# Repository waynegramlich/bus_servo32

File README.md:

# bus_servo32

This is really a template for `bus_servoN` modules, where
N is a multiple of 4.

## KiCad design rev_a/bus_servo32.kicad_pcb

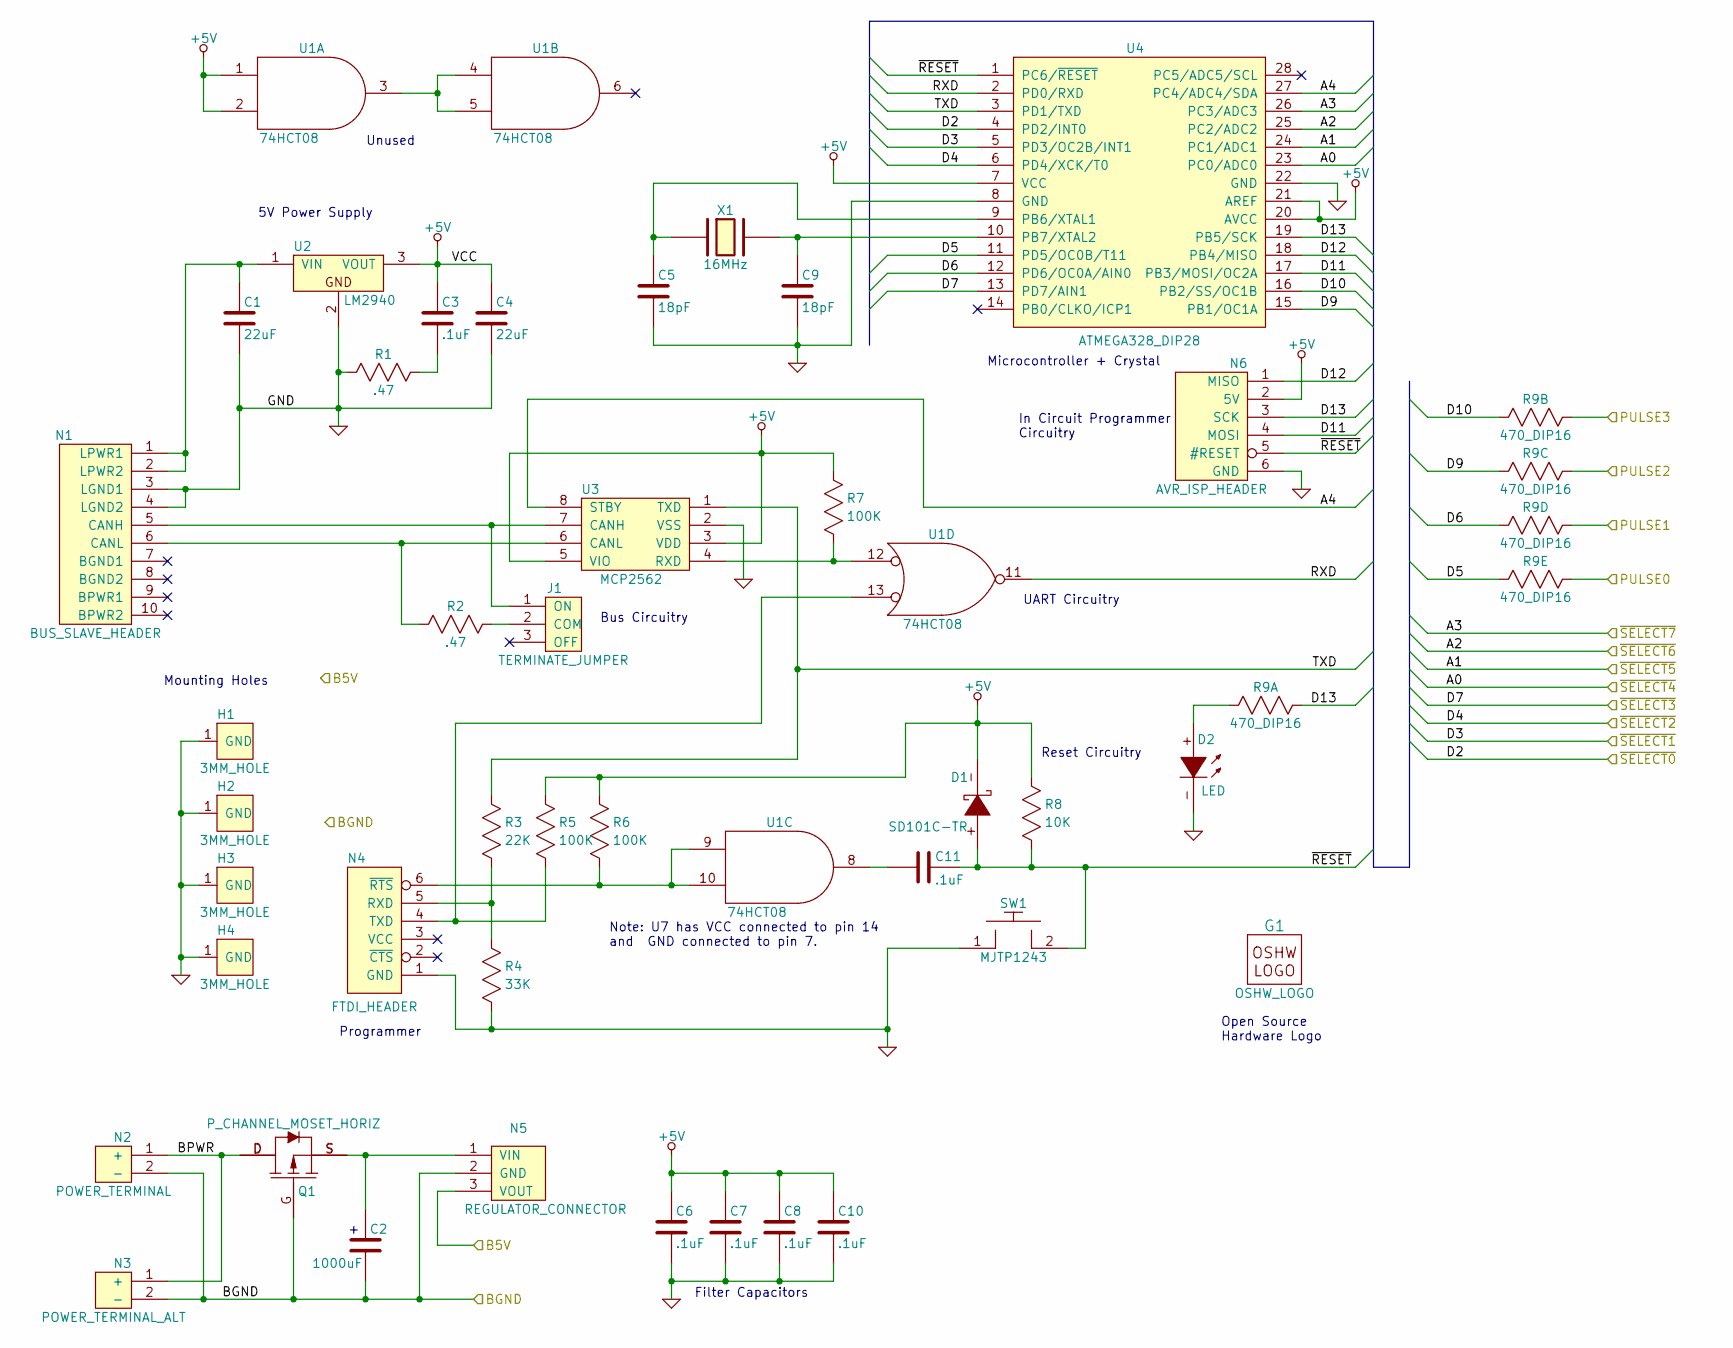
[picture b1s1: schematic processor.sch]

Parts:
C1, C4: 22uF; Capacitor3MMDiscRM2.5
C2: 1000uF; Capacitor4x3RM2-5_RevB
C3, C6, C7, C8, C10, C11: .1uF; Capacitor4x3RM2-5_RevB
C5, C9: 18pF; Capacitor4x3RM2-5_RevB
D1: SD101C-TR; Diode_DO-41_SOD81_Horizontal_RM10
D2: LED; T1_LED
G1: OSHW_LOGO; OSHW_LOGO_300mil
H1, H2, H3, H4: 3MM_HOLE; MountingHole_3mm
J1: TERMINATE_JUMPER; Pin_Header_Straight_1x03
N1: BUS_SLAVE_HEADER; Pin_Header_Straight_2x05_Shrouded
N2: POWER_TERMINAL; 5MM_TERMINAL_BLOCK_2_POS
N3: POWER_TERMINAL_ALT; 5MM_TERMINAL_BLOCK_2_POS
N4: FTDI_HEADER; Pin_Header_Straight_1x06
N5: REGULATOR_CONNECTOR; Pin_Header_Straight_1x03
N6: AVR_ISP_HEADER; Pin_Header_Straight_2x03
Q1: P_CHANNEL_MOSET_HORIZ; TO-220_Neutral123_Horizontal_LargePads
R1, R2: .47; Resistor_Horizontal_400
R3: 22K; Resistor_Horizontal_400
R4: 33K; Resistor_Horizontal_400
R5, R6, R7: 100K; Resistor_Horizontal_400
R8: 10K; Resistor_Horizontal_400
R9: 470_DIP16; DIP-16__300
SW1: MJTP1243; Button_6.5MM
U1: 74HCT08; DIP-14__300
U2: LM2940; TO-220_Neutral123_Horizontal_LargePads
U3: MCP2562; DIP-8__300
U4: ATMEGA328_DIP28; DIP-28__300
X1: 16MHz; Crystal_HC49-U_Vertical

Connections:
+5V: C3.1, C4.1, C6.1, C7.1, C8.1, C10.1, D1.-, N6.2 (5V), R5.2, R6.2, R7.2, R8.2, U1.1, U1.2, U1.14 (VCC), U2.3 (VOUT), U3.3 (VDD), U3.5 (VIO), U4.7 (VCC), U4.20 (AVCC), U4.21 (AREF)
/Processor/A4: U3.8 (STBY), U4.27 (PC4/ADC4/SDA)
/Processor/B5V: N5.3 (VOUT); also elsewhere on the board
/Processor/BGND: C2.2, N2.2 (-), N3.2 (-), N5.2 (GND), Q1.G; also elsewhere on the board
/Processor/BPWR: N2.1 (+), N3.1 (+), Q1.D
/Processor/D5: R9.5 (A), U4.11 (PD5/OC0B/T11)
/Processor/D6: R9.4 (A), U4.12 (PD6/OC0A/AIN0)
/Processor/D9: R9.3 (A), U4.15 (PB1/OC1A)
/Processor/D10: R9.2 (A), U4.16 (PB2/SS/OC1B)
/Processor/D11: N6.4 (MOSI), U4.17 (PB3/MOSI/OC2A)
/Processor/D12: N6.1 (MISO), U4.18 (PB4/MISO)
/Processor/D13: N6.3 (SCK), R9.16 (B), U4.19 (PB5/SCK)
/Processor/PULSE0: R9.12 (B); also elsewhere on the board
/Processor/PULSE1: R9.13 (B); also elsewhere on the board
/Processor/PULSE2: R9.14 (B); also elsewhere on the board
/Processor/PULSE3: R9.15 (B); also elsewhere on the board
/Processor/RXD: U1.11, U4.2 (PD0/RXD)
/Processor/TXD: R3.2, U3.1 (TXD), U4.3 (PD1/TXD)
/Processor/~RESET: C11.2, D1.+, N6.5 (#RESET), R8.1, SW1.2, U4.1 (PC6/~RESET)
/Processor/~SELECT0: U4.4 (PD2/INT0); also elsewhere on the board
/Processor/~SELECT1: U4.5 (PD3/OC2B/INT1); also elsewhere on the board
/Processor/~SELECT2: U4.6 (PD4/XCK/T0); also elsewhere on the board
/Processor/~SELECT3: U4.13 (PD7/AIN1); also elsewhere on the board
/Processor/~SELECT4: U4.23 (PC0/ADC0); also elsewhere on the board
/Processor/~SELECT5: U4.24 (PC1/ADC1); also elsewhere on the board
/Processor/~SELECT6: U4.25 (PC2/ADC2); also elsewhere on the board
/Processor/~SELECT7: U4.26 (PC3/ADC3); also elsewhere on the board
GND: C1.2, C4.2, C5.2, C6.2, C7.2, C8.2, C9.2, C10.2, D2.-, H1.1, H2.1, H3.1, H4.1, N1.3 (LGND1), N1.4 (LGND2), N4.1 (GND), N6.6 (GND), R1.1, R4.1, SW1.1, U1.7 (GND), U2.2, U3.2 (VSS), U4.8 (GND), U4.22 (GND)
unnamed: C1.1, N1.1 (LPWR1), N1.2 (LPWR2), U2.1 (VIN)
unnamed: C2.1, N5.1 (VIN), Q1.S
unnamed: C3.2, R1.2
unnamed: C5.1, U4.9 (PB6/XTAL1), X1.1
unnamed: C9.1, U4.10 (PB7/XTAL2), X1.2
unnamed: C11.1, U1.8
unnamed: D2.+, R9.1 (A)
unnamed: J1.1 (ON), N1.5 (CANH), U3.7 (CANH)
unnamed: J1.2 (COM), R2.2
unnamed: N1.6 (CANL), R2.1, U3.6 (CANL)
unnamed: N4.4 (TXD), R5.1, U1.13
unnamed: N4.5 (RXD), R3.1, R4.2
unnamed: N4.6 (~RTS), R6.1, U1.9, U1.10
unnamed: R7.1, U1.12, U3.4 (RXD)
unnamed: U1.3, U1.4, U1.5

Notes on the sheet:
Filter Capacitors
Reset Circuitry
Programmer
UART Circuitry
5V Power Supply
Unused
Note: U7 has VCC connected to pin 14 and GND connected to pin 7.
In Circuit Programmer Circuitry
Bus Circuitry
Mounting Holes
Open Source Hardware Logo
Microcontroller + Crystal

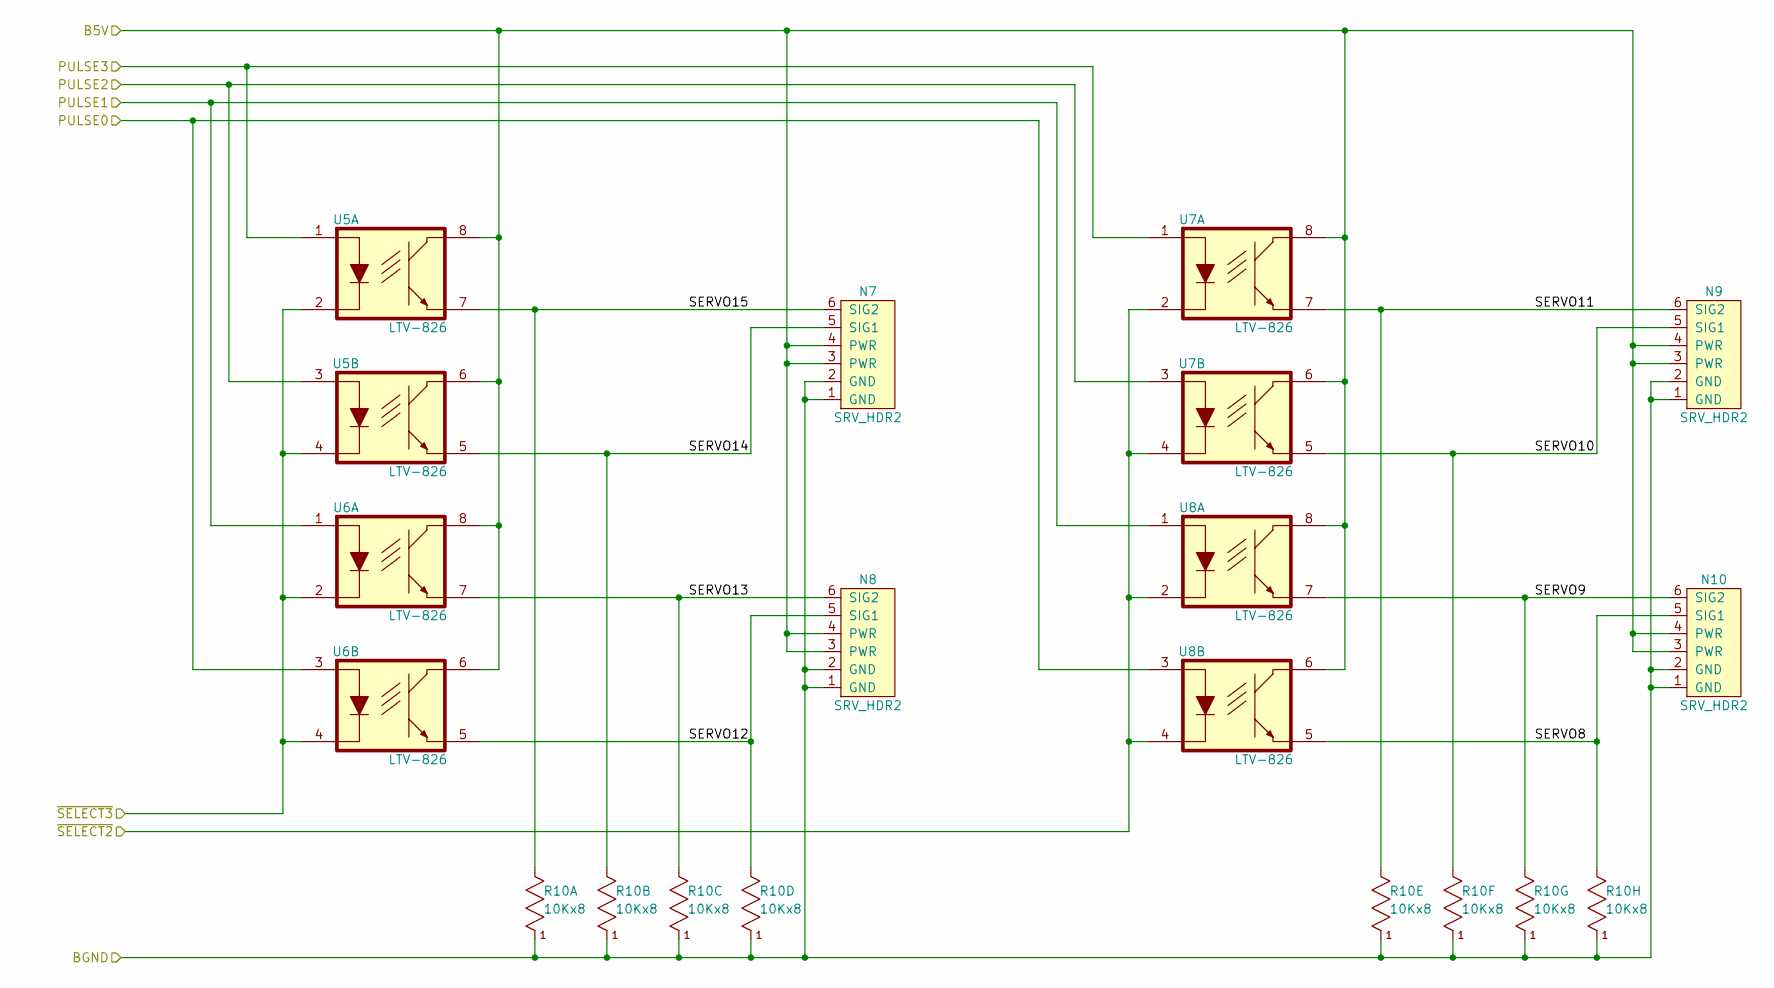
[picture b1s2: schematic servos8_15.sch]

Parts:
N7, N8, N9, N10: SRV_HDR2; Pin_Header_Straight_2x03
R10: 10Kx8; Pin_Header_Straight_1x09
U5, U6, U7, U8: LTV-826; DIP-8__300

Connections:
/Processor/B5V: N7.3 (PWR), N7.4 (PWR), N8.3 (PWR), N8.4 (PWR), N9.3 (PWR), N9.4 (PWR), N10.3 (PWR), N10.4 (PWR), U5.6, U5.8, U6.6, U6.8, U7.6, U7.8, U8.6, U8.8; also elsewhere on the board
/Processor/BGND: N7.1 (GND), N7.2 (GND), N8.1 (GND), N8.2 (GND), N9.1 (GND), N9.2 (GND), N10.1 (GND), N10.2 (GND), R10.1; also elsewhere on the board
/Processor/PULSE0: U6.3, U8.3; also elsewhere on the board
/Processor/PULSE1: U6.1, U8.1; also elsewhere on the board
/Processor/PULSE2: U5.3, U7.3; also elsewhere on the board
/Processor/PULSE3: U5.1, U7.1; also elsewhere on the board
/Processor/~SELECT2: U7.2, U7.4, U8.2, U8.4; also elsewhere on the board
/Processor/~SELECT3: U5.2, U5.4, U6.2, U6.4; also elsewhere on the board
/Servos_8:15/SERVO8: N10.5 (SIG1), R10.9, U8.5
/Servos_8:15/SERVO9: N10.6 (SIG2), R10.8, U8.7
/Servos_8:15/SERVO10: N9.5 (SIG1), R10.7, U7.5
/Servos_8:15/SERVO11: N9.6 (SIG2), R10.6, U7.7
/Servos_8:15/SERVO12: N8.5 (SIG1), R10.5, U6.5
/Servos_8:15/SERVO13: N8.6 (SIG2), R10.4, U6.7
/Servos_8:15/SERVO14: N7.5 (SIG1), R10.3, U5.5
/Servos_8:15/SERVO15: N7.6 (SIG2), R10.2, U5.7

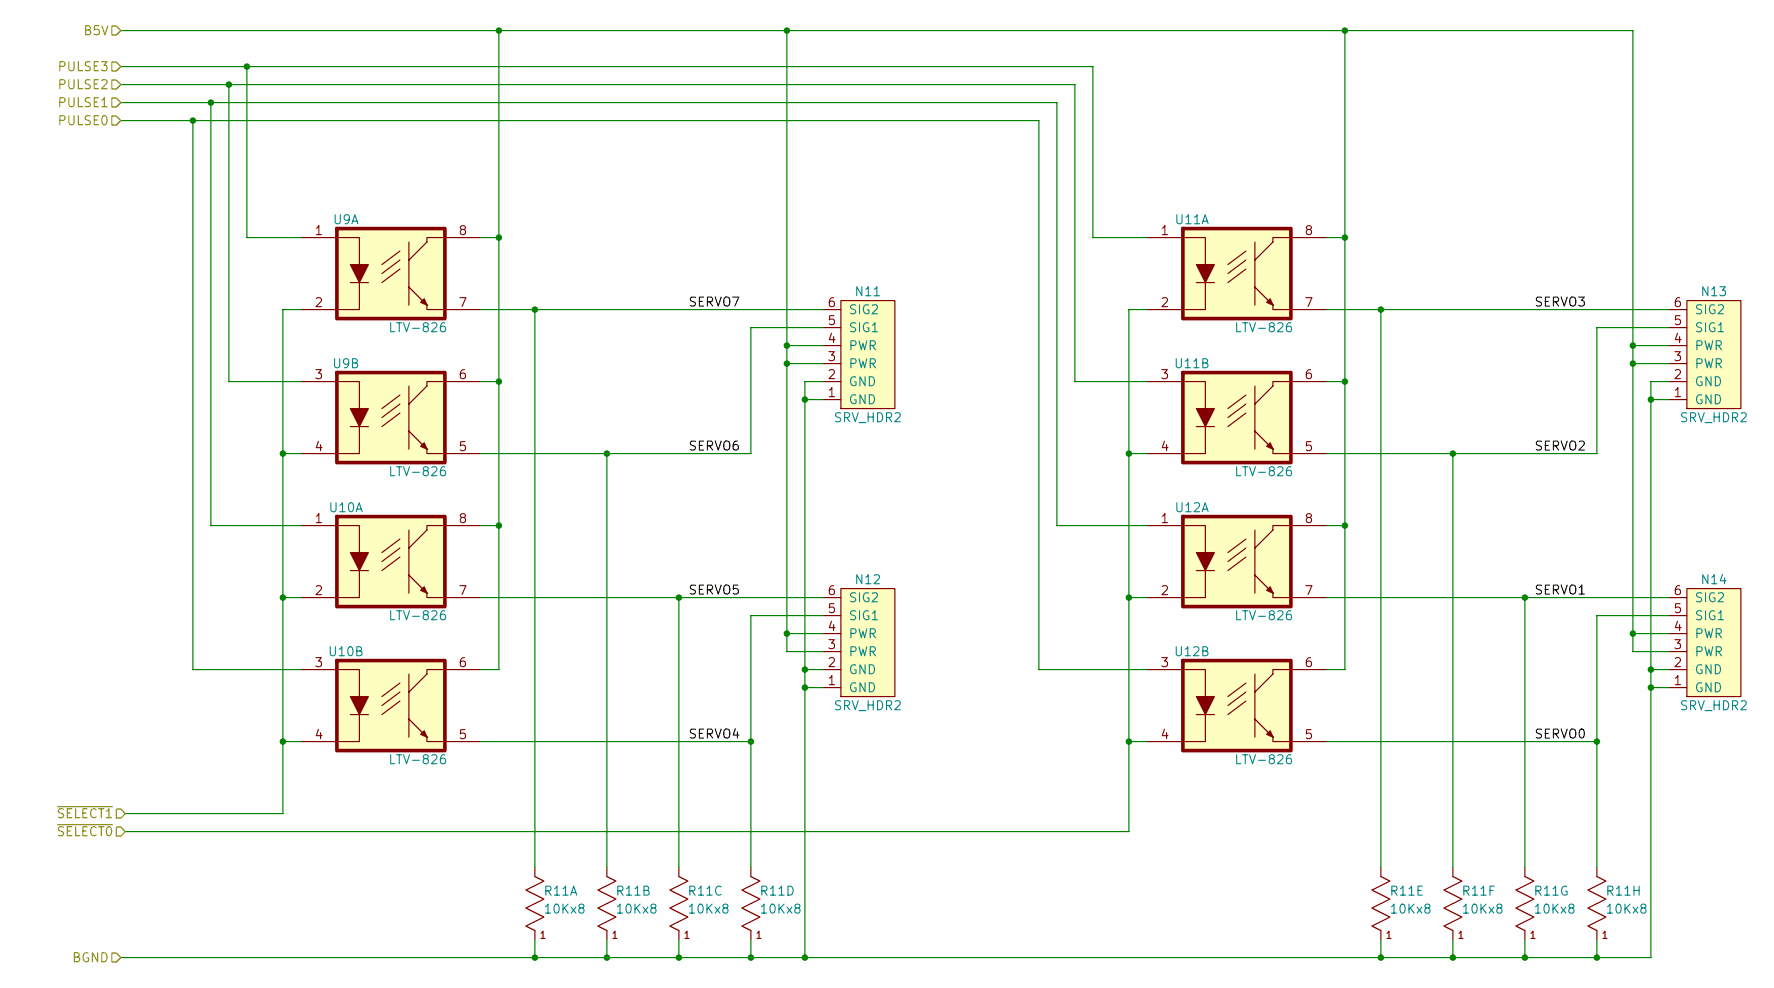
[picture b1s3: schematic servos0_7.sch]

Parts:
N11, N12, N13, N14: SRV_HDR2; Pin_Header_Straight_2x03
R11: 10Kx8; Pin_Header_Straight_1x09
U9, U10, U11, U12: LTV-826; DIP-8__300

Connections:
/Processor/B5V: N11.3 (PWR), N11.4 (PWR), N12.3 (PWR), N12.4 (PWR), N13.3 (PWR), N13.4 (PWR), N14.3 (PWR), N14.4 (PWR), U9.6, U9.8, U10.6, U10.8, U11.6, U11.8, U12.6, U12.8; also elsewhere on the board
/Processor/BGND: N11.1 (GND), N11.2 (GND), N12.1 (GND), N12.2 (GND), N13.1 (GND), N13.2 (GND), N14.1 (GND), N14.2 (GND), R11.1; also elsewhere on the board
/Processor/PULSE0: U10.3, U12.3; also elsewhere on the board
/Processor/PULSE1: U10.1, U12.1; also elsewhere on the board
/Processor/PULSE2: U9.3, U11.3; also elsewhere on the board
/Processor/PULSE3: U9.1, U11.1; also elsewhere on the board
/Processor/~SELECT0: U11.2, U11.4, U12.2, U12.4; also elsewhere on the board
/Processor/~SELECT1: U9.2, U9.4, U10.2, U10.4; also elsewhere on the board
/Servos_0:7/SERVO0: N14.5 (SIG1), R11.9, U12.5
/Servos_0:7/SERVO1: N14.6 (SIG2), R11.8, U12.7
/Servos_0:7/SERVO2: N13.5 (SIG1), R11.7, U11.5
/Servos_0:7/SERVO3: N13.6 (SIG2), R11.6, U11.7
/Servos_0:7/SERVO4: N12.5 (SIG1), R11.5, U10.5
/Servos_0:7/SERVO5: N12.6 (SIG2), R11.4, U10.7
/Servos_0:7/SERVO6: N11.5 (SIG1), R11.3, U9.5
/Servos_0:7/SERVO7: N11.6 (SIG2), R11.2, U9.7

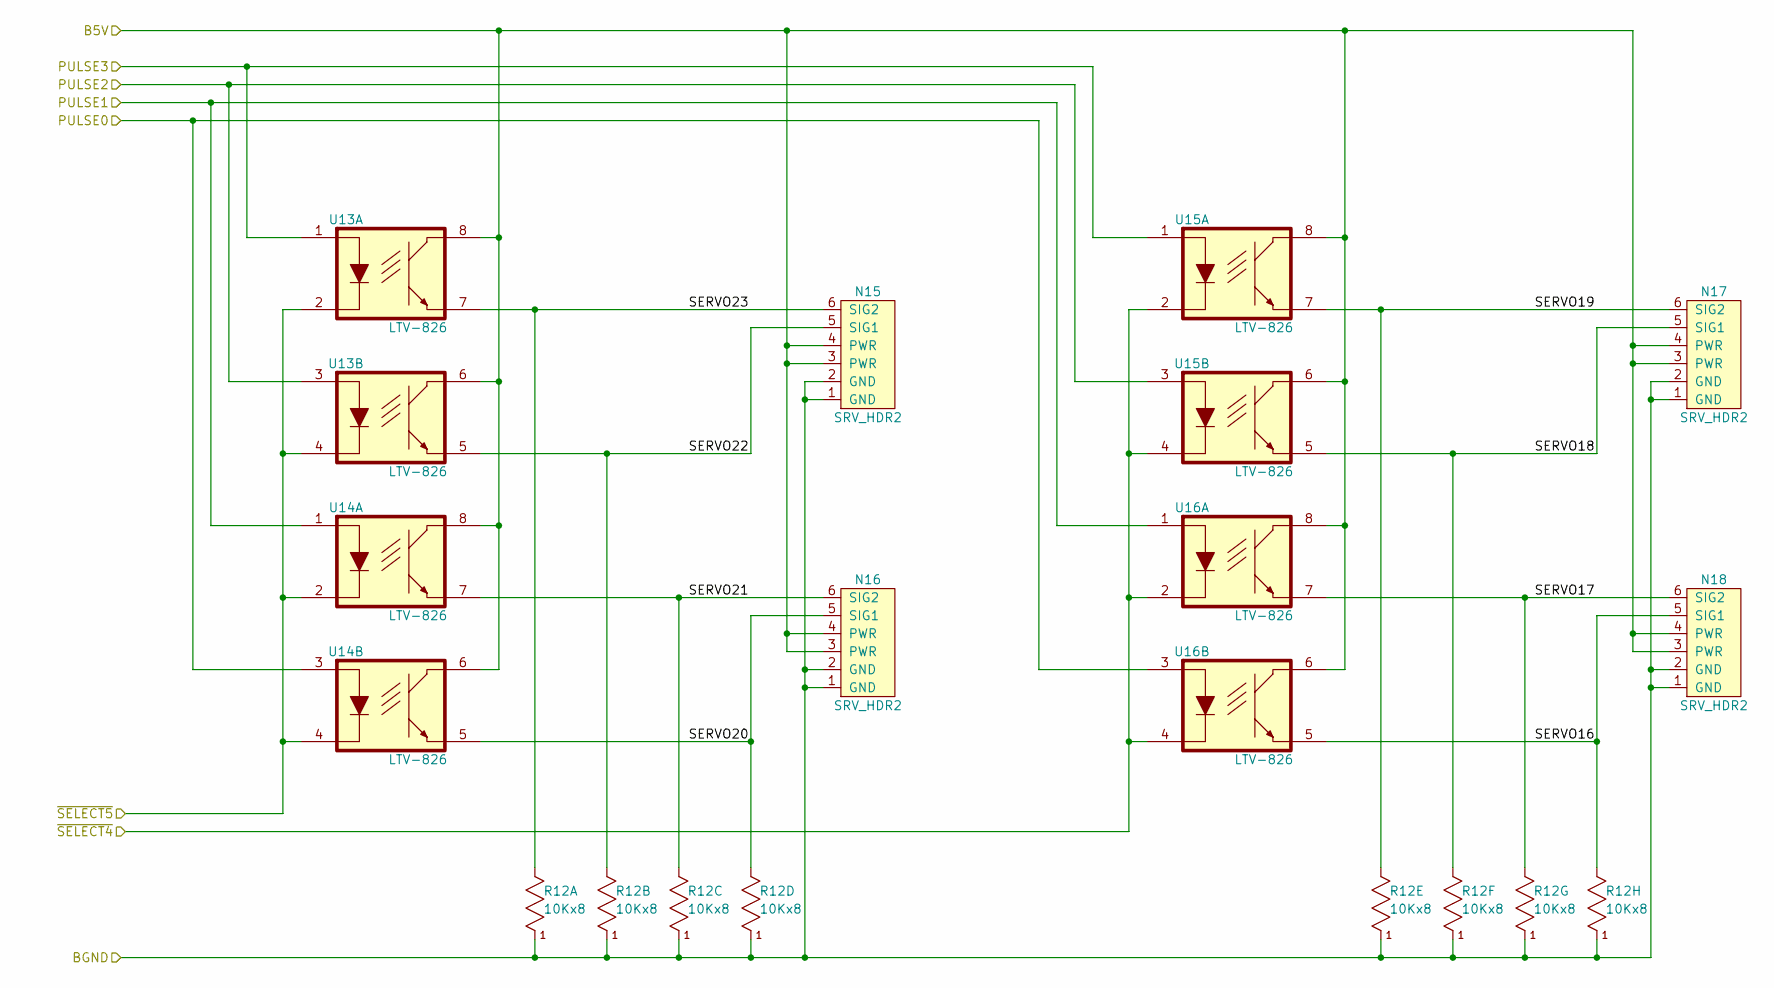
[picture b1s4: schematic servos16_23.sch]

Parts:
N15, N16, N17, N18: SRV_HDR2; Pin_Header_Straight_2x03
R12: 10Kx8; Pin_Header_Straight_1x09
U13, U14, U15, U16: LTV-826; DIP-8__300

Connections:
/Processor/B5V: N15.3 (PWR), N15.4 (PWR), N16.3 (PWR), N16.4 (PWR), N17.3 (PWR), N17.4 (PWR), N18.3 (PWR), N18.4 (PWR), U13.6, U13.8, U14.6, U14.8, U15.6, U15.8, U16.6, U16.8; also elsewhere on the board
/Processor/BGND: N15.1 (GND), N15.2 (GND), N16.1 (GND), N16.2 (GND), N17.1 (GND), N17.2 (GND), N18.1 (GND), N18.2 (GND), R12.1; also elsewhere on the board
/Processor/PULSE0: U14.3, U16.3; also elsewhere on the board
/Processor/PULSE1: U14.1, U16.1; also elsewhere on the board
/Processor/PULSE2: U13.3, U15.3; also elsewhere on the board
/Processor/PULSE3: U13.1, U15.1; also elsewhere on the board
/Processor/~SELECT4: U15.2, U15.4, U16.2, U16.4; also elsewhere on the board
/Processor/~SELECT5: U13.2, U13.4, U14.2, U14.4; also elsewhere on the board
/Servos_16:23/SERVO16: N18.5 (SIG1), R12.9, U16.5
/Servos_16:23/SERVO17: N18.6 (SIG2), R12.8, U16.7
/Servos_16:23/SERVO18: N17.5 (SIG1), R12.7, U15.5
/Servos_16:23/SERVO19: N17.6 (SIG2), R12.6, U15.7
/Servos_16:23/SERVO20: N16.5 (SIG1), R12.5, U14.5
/Servos_16:23/SERVO21: N16.6 (SIG2), R12.4, U14.7
/Servos_16:23/SERVO22: N15.5 (SIG1), R12.3, U13.5
/Servos_16:23/SERVO23: N15.6 (SIG2), R12.2, U13.7

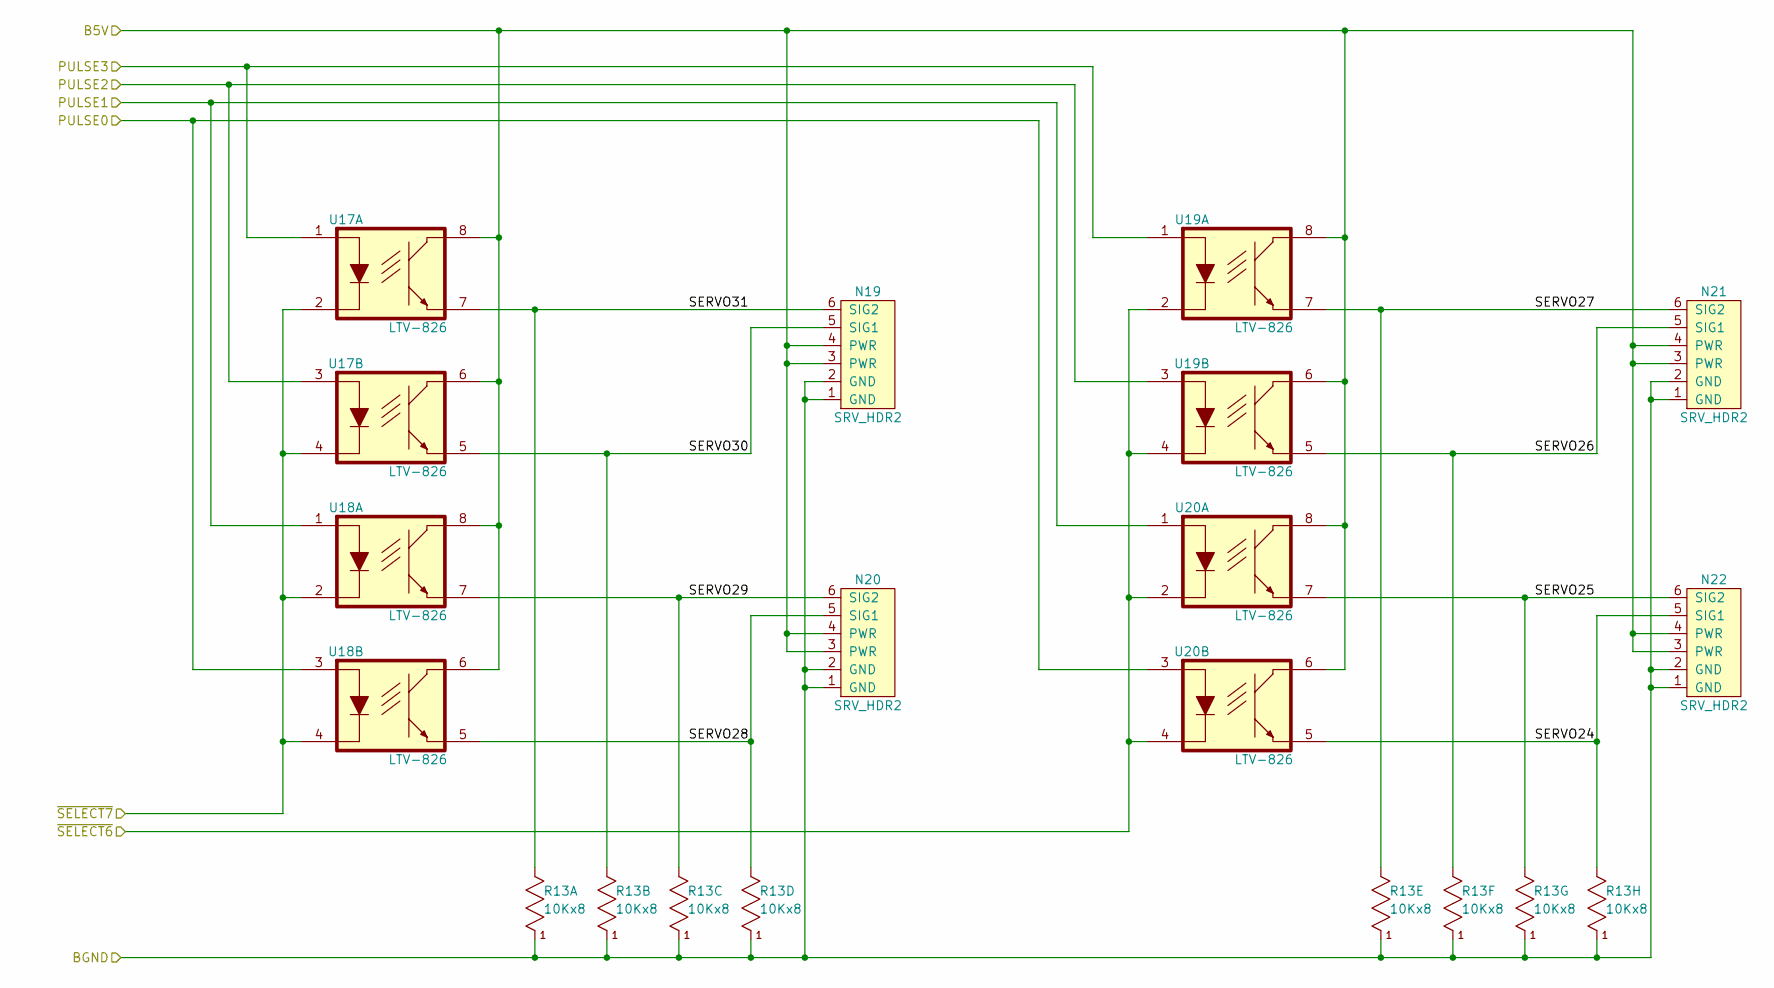
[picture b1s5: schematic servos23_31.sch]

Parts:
N19, N20, N21, N22: SRV_HDR2; Pin_Header_Straight_2x03
R13: 10Kx8; Pin_Header_Straight_1x09
U17, U18, U19, U20: LTV-826; DIP-8__300

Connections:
/Processor/B5V: N19.3 (PWR), N19.4 (PWR), N20.3 (PWR), N20.4 (PWR), N21.3 (PWR), N21.4 (PWR), N22.3 (PWR), N22.4 (PWR), U17.6, U17.8, U18.6, U18.8, U19.6, U19.8, U20.6, U20.8; also elsewhere on the board
/Processor/BGND: N19.1 (GND), N19.2 (GND), N20.1 (GND), N20.2 (GND), N21.1 (GND), N21.2 (GND), N22.1 (GND), N22.2 (GND), R13.1; also elsewhere on the board
/Processor/PULSE0: U18.3, U20.3; also elsewhere on the board
/Processor/PULSE1: U18.1, U20.1; also elsewhere on the board
/Processor/PULSE2: U17.3, U19.3; also elsewhere on the board
/Processor/PULSE3: U17.1, U19.1; also elsewhere on the board
/Processor/~SELECT6: U19.2, U19.4, U20.2, U20.4; also elsewhere on the board
/Processor/~SELECT7: U17.2, U17.4, U18.2, U18.4; also elsewhere on the board
/Servos_23:32/SERVO24: N22.5 (SIG1), R13.9, U20.5
/Servos_23:32/SERVO25: N22.6 (SIG2), R13.8, U20.7
/Servos_23:32/SERVO26: N21.5 (SIG1), R13.7, U19.5
/Servos_23:32/SERVO27: N21.6 (SIG2), R13.6, U19.7
/Servos_23:32/SERVO28: N20.5 (SIG1), R13.5, U18.5
/Servos_23:32/SERVO29: N20.6 (SIG2), R13.4, U18.7
/Servos_23:32/SERVO30: N19.5 (SIG1), R13.3, U17.5
/Servos_23:32/SERVO31: N19.6 (SIG2), R13.2, U17.7

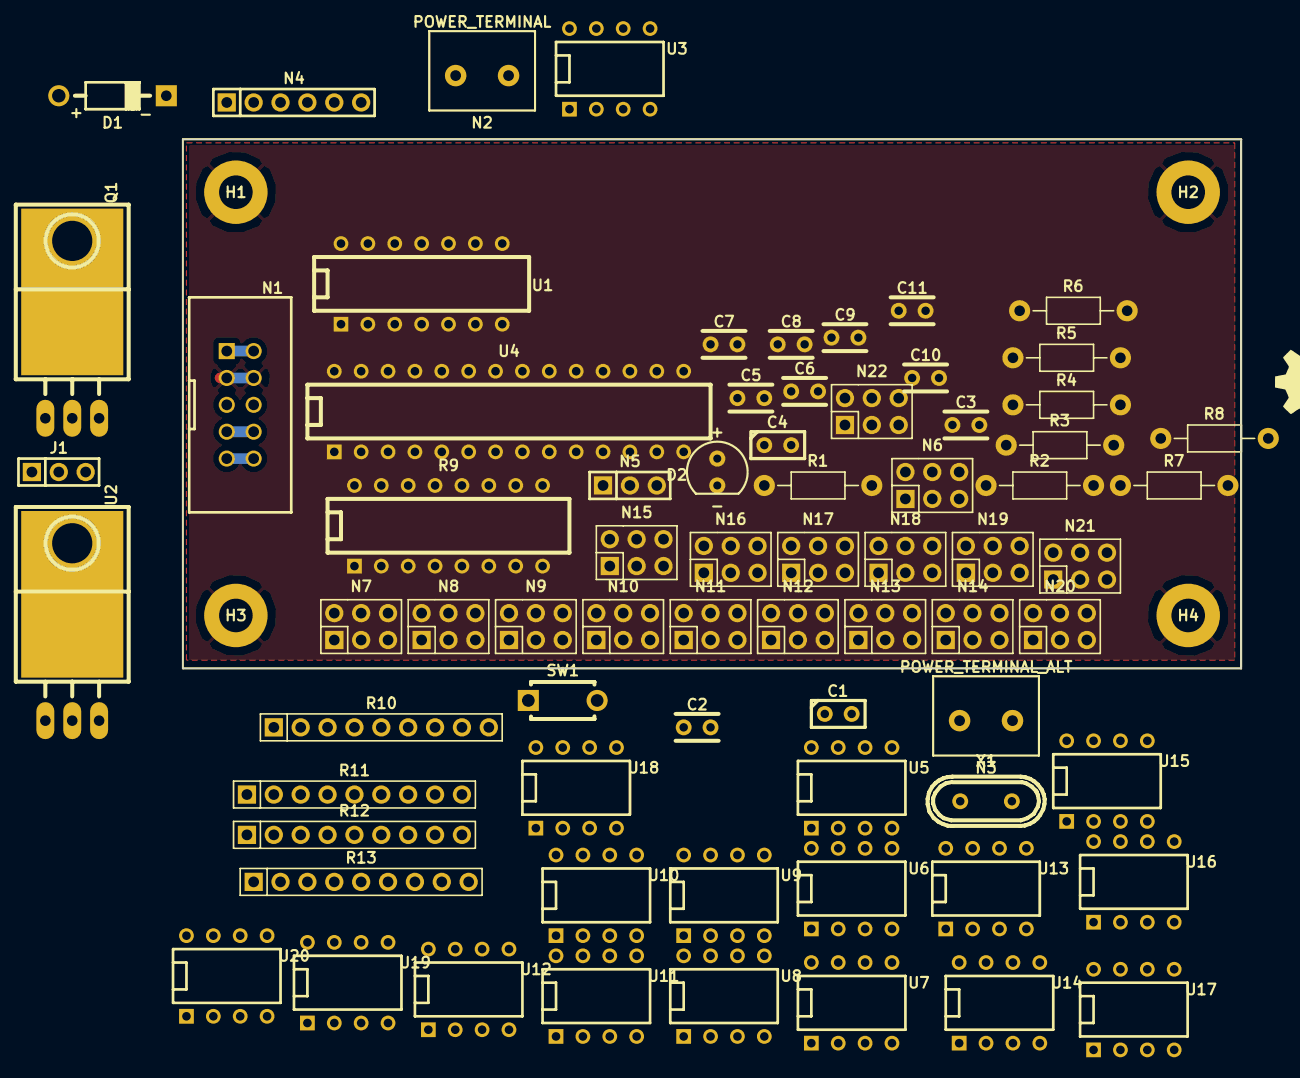
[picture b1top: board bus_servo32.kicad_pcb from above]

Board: 2 copper layers, 100.0 x 50.0 mm, 77 parts (0 on the bottom side), 75 nets.

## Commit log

2015-01-25 Save everything in its current imcomplete state.
2015-01-25 Fixed README.md
